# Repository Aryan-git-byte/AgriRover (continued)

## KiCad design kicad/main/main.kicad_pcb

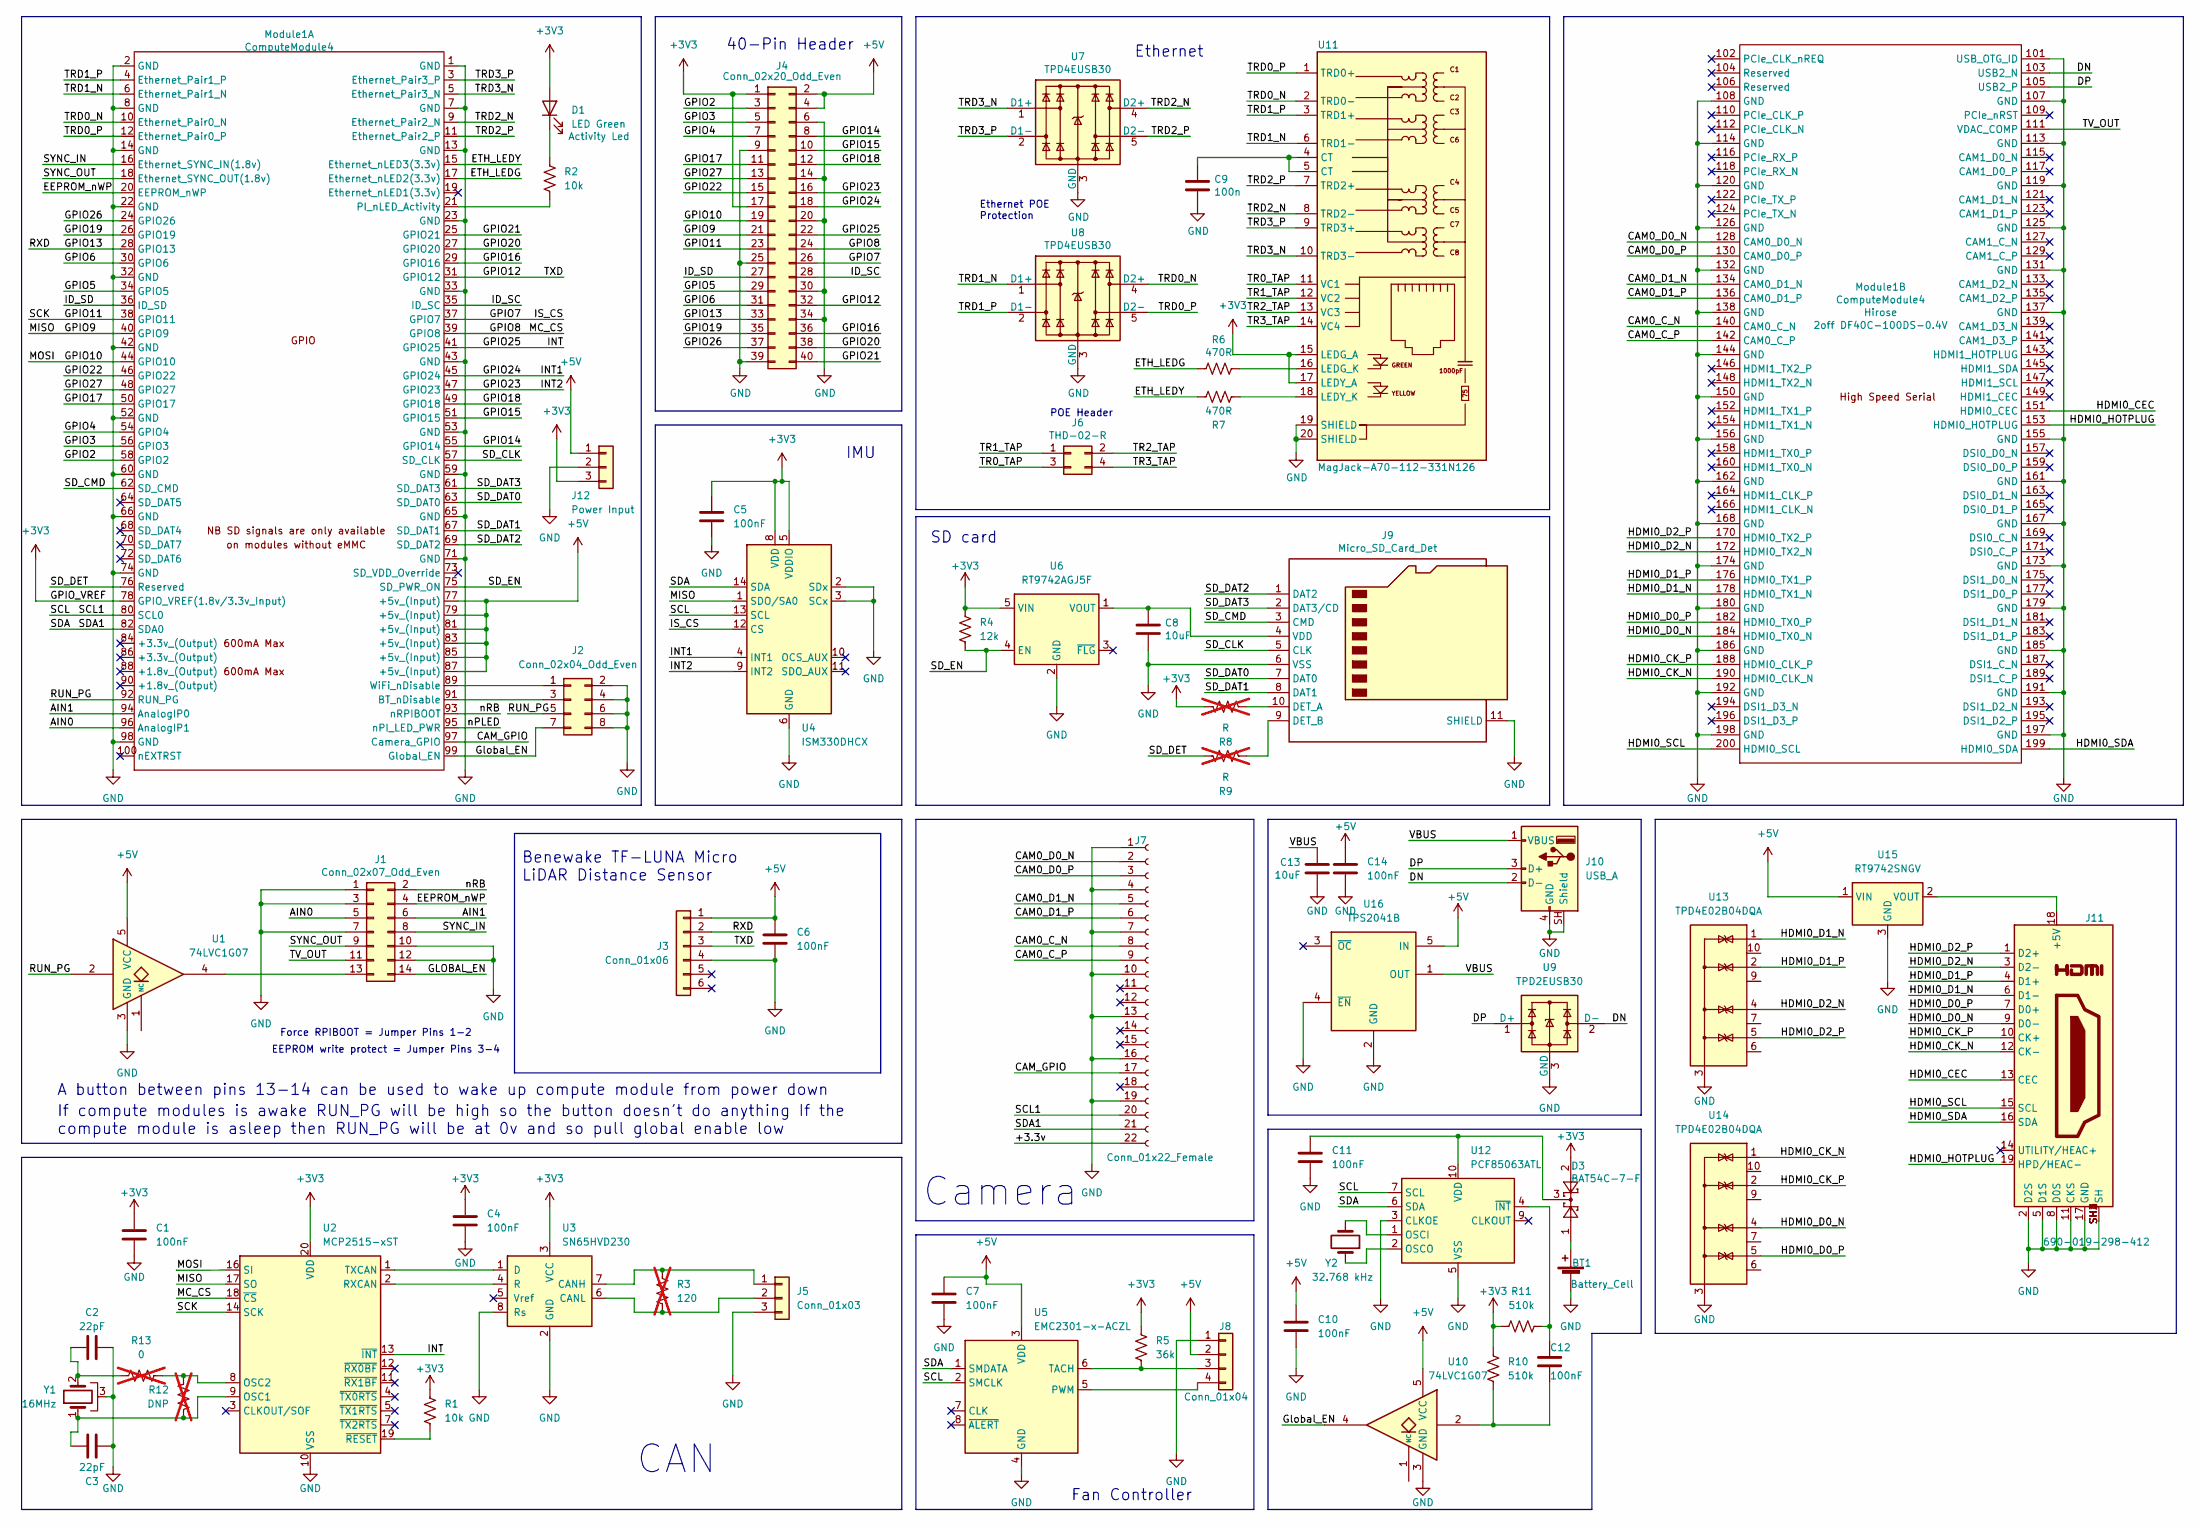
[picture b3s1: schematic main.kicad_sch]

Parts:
BT1: Battery_Cell; BatteryHolder_Keystone_3034_1x20mm; Part Description Battery Retainer Coin, 20.0mm 1 Cell SM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
C1, C4, C5, C6, C7, C10, C11, C12, C14: 100nF; C_0603_1608Metric
C2, C3: 22pF; C_0603_1608Metric
C8, C13: 10uF; C_0805_2012Metric; Part Description 10uF 10% 10V Ceramic Capacitor X7R 0805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
C9: 100n; C_0402_1005Metric; Part Description 0.1uF 10% 16V Ceramic Capacitor X7R 040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
D1: LED Green; LED_0805_2012Metric
D3: BAT54C-7-F; SOT-23; Part Description Diode Array 1 Pair Common Cathode Schot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
J1: Conn_02x07_Odd_Even; PinHeader_2x07_P2.54mm_Vertical; Part Description PinHeader_2x07_P2.54mm_Vertical
J2: Conn_02x04_Odd_Even; PinHeader_2x04_P2.54mm_Vertical
J3: Conn_01x06; Molex_PicoBlade_53047-0610_1x06_P1.25mm_Vertical
J4: Conn_02x20_Odd_Even; PinHeader_2x20_P2.54mm_Vertical; Part Description PinHeader_2x20_P2.54mm_Vertical
J5: Conn_01x03; FanPinHeader_1x03_P2.54mm_Vertical
J6: THD-02-R; PinHeader_2x02_P2.54mm_Vertical; Part Description PinHeader_2x02_P2.54mm_Vertical
J7: Conn_01x22_Female; Hirose_FH12-22S-0.5SH_1x22-1MP_P0.50mm_Horizontal; Part Description 22 Position FFC, FPC Connector Contacts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
J8: Conn_01x04; FanPinHeader_1x04_P2.54mm_Vertical
J9: Micro_SD_Card_Det; SDCARD_MOLEX_503398-1892; Part Description 9 (8 + 1) Position Card Connector micro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
J10: USB_A; USB_A_Connfly_DS1095
J11: 690-019-298-412; EDAC 690-019-298-412; Part Description HDMI Connector, Right Angle, 19 Contact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
J12: Power Input; JST_XH_B3B-XH-A_1x03_P2.50mm_Vertical
Module1: ComputeModule4; Raspberry-Pi-4-Compute-Module; Part Description 100 Position Connector Receptacle, Cent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
R1, R2: 10k; R_0603_1608Metric
R3: 120; R_0603_1608Metric; not fitted
R4: 12k; R_0603_1608Metric
R5: 36k; R_0603_1608Metric
R6, R7: 470R; R_0603_1608Metric; Part Description Resistor 470R M1005 1% 63mW
R8, R9: R; R_0603_1608Metric; not fitted
R10, R11: 510k; R_0603_1608Metric
R12: DNP; R_0603_1608Metric; not fitted
R13: 0; R_0603_1608Metric; not fitted
U1, U10: 74LVC1G07; SOT-23-5
U2: MCP2515-xST; TSSOP-20_4.4x6.5mm_P0.65mm
U3: SN65HVD230; SOIC-8_3.9x4.9mm_P1.27mm
U4: ISM330DHCX; LGA-14_3x2.5mm_P0.5mm_LayoutBorder3x4y
U5: EMC2301-x-ACZL; MSOP-8_3x3mm_P0.65mm
U6: RT9742AGJ5F; TSOT-23-5
U7, U8: TPD4EUSB30; USON-10_2.5x1.0mm_P0.5mm; Part Description Quad TVS diode for high speed signals (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
U9: TPD2EUSB30; Texas_DRT-3
U11: MagJack-A70-112-331N126; TRJG0926HENL; Part Description Gigabit Ethernet Magjack
U12: PCF85063ATL; DFN-10-1EP_2.6x2.6mm_P0.5mm_EP1.3x2.2mm
U13, U14: TPD4E02B04DQA; USON-10_2.5x1.0mm_P0.5mm
U15: RT9742SNGV; SOT-23-3
U16: TPS2041B; SOT-23-5
Y1: 16MHz; Crystal_SMD_3225-4Pin_3.2x2.5mm
Y2: 32.768 kHz; Crystal_SMD_3215-2Pin_3.2x1.5mm

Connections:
+3V3: C1.1, C4.1, C5.1, D1.2 (A), D3.2, J4.1, J4.17, J12.3, Module1.78 (GPIO_VREF(1.8v/3.3v_Input)), R1.1, R4.1, R5.1, R8.1, R10.1, R11.1, U2.20 (VDD), U3.3 (VCC), U4.5 (VDDIO), U4.8 (VDD), U6.5 (VIN), U11.15 (LEDG_A), U11.17 (LEDY_A)
+5V: C6.1, C7.1, C10.1, C14.1, J3.1, J4.2, J4.4, J8.2, J12.1, Module1.77 (+5v_(Input)), Module1.79 (+5v_(Input)), Module1.81 (+5v_(Input)), Module1.83 (+5v_(Input)), Module1.85 (+5v_(Input)), Module1.87 (+5v_(Input)), U1.5 (VCC), U5.3 (VDD), U10.5 (VCC), U15.1 (VIN), U16.5 (IN)
/+3.3v: J7.22
/AIN0: J1.5, Module1.96 (AnalogIP1)
/AIN1: J1.6, Module1.94 (AnalogIP0)
/CAM0_C_N: J7.8, Module1.140 (CAM0_C_N)
/CAM0_C_P: J7.9, Module1.142 (CAM0_C_P)
/CAM0_D0_N: J7.2, Module1.128 (CAM0_D0_N)
/CAM0_D0_P: J7.3, Module1.130 (CAM0_D0_P)
/CAM0_D1_N: J7.5, Module1.134 (CAM0_D1_N)
/CAM0_D1_P: J7.6, Module1.136 (CAM0_D1_P)
/CAM_GPIO: J7.17, Module1.97 (Camera_GPIO)
/DN: J10.2 (D-), Module1.103 (USB2_N), U9.2 (D-)
/DP: J10.3 (D+), Module1.105 (USB2_P), U9.1 (D+)
/EEPROM_nWP: J1.4, Module1.20 (EEPROM_nWP)
/ETH_LEDG: Module1.17 (Ethernet_nLED2(3.3v)), R6.2
/ETH_LEDY: Module1.15 (Ethernet_nLED3(3.3v)), R7.2
/GLOBAL_EN: J1.14
/GPIO2: J4.3, Module1.58 (GPIO2)
/GPIO3: J4.5, Module1.56 (GPIO3)
/GPIO4: J4.7, Module1.54 (GPIO4)
/GPIO5: J4.29, Module1.34 (GPIO5)
/GPIO6: J4.31, Module1.30 (GPIO6)
/GPIO7: J4.26, Module1.37 (GPIO7), U4.12 (CS)
/GPIO8: J4.24, Module1.39 (GPIO8), U2.18 (~CS)
/GPIO9: J4.21, Module1.40 (GPIO9), U2.17 (SO), U4.1 (SDO/SA0)
/GPIO10: J4.19, Module1.44 (GPIO10), U2.16 (SI)
/GPIO11: J4.23, Module1.38 (GPIO11), U2.14 (SCK)
/GPIO12: J3.3, J4.32, Module1.31 (GPIO12)
/GPIO13: J3.2, J4.33, Module1.28 (GPIO13)
/GPIO14: J4.8, Module1.55 (GPIO14)
/GPIO15: J4.10, Module1.51 (GPIO15)
/GPIO16: J4.36, Module1.29 (GPIO16)
/GPIO17: J4.11, Module1.50 (GPIO17)
/GPIO18: J4.12, Module1.49 (GPIO18)
/GPIO19: J4.35, Module1.26 (GPIO19)
/GPIO20: J4.38, Module1.27 (GPIO20)
/GPIO21: J4.40, Module1.25 (GPIO21)
/GPIO22: J4.15, Module1.46 (GPIO22)
/GPIO23: J4.16, Module1.47 (GPIO23), U4.9 (INT2)
/GPIO24: J4.18, Module1.45 (GPIO24), U4.4 (INT1)
/GPIO25: J4.22, Module1.41 (GPIO25), U2.13 (~INT)
/GPIO26: J4.37, Module1.24 (GPIO26)
/GPIO27: J4.13, Module1.48 (GPIO27)
/Global_EN: J2.7, Module1.99 (Global_EN), U10.4
/HDMI0_CEC: J11.13 (CEC), Module1.151 (HDMI0_CEC)
/HDMI0_CK_N: J11.12 (CK-), Module1.190 (HDMI0_CLK_N), U14.1 (IO1)
/HDMI0_CK_P: J11.10 (CK+), Module1.188 (HDMI0_CLK_P), U14.2 (IO2)
/HDMI0_D0_N: J11.9 (D0-), Module1.184 (HDMI0_TX0_N), U14.4 (IO3)
/HDMI0_D0_P: J11.7 (D0+), Module1.182 (HDMI0_TX0_P), U14.5 (IO4)
/HDMI0_D1_N: J11.6 (D1-), Module1.178 (HDMI0_TX1_N), U13.1 (IO1)
/HDMI0_D1_P: J11.4 (D1+), Module1.176 (HDMI0_TX1_P), U13.2 (IO2)
/HDMI0_D2_N: J11.3 (D2-), Module1.172 (HDMI0_TX2_N), U13.4 (IO3)
/HDMI0_D2_P: J11.1 (D2+), Module1.170 (HDMI0_TX2_P), U13.5 (IO4)
/HDMI0_HOTPLUG: J11.19 (HPD/HEAC-), Module1.153 (HDMI0_HOTPLUG)
/HDMI0_SCL: J11.15 (SCL), Module1.200 (HDMI0_SCL)
/HDMI0_SDA: J11.16 (SDA), Module1.199 (HDMI0_SDA)
/ID_SC: J4.28, Module1.35 (ID_SC)
/ID_SD: J4.27, Module1.36 (ID_SD)
/RUN_PG: J2.5, Module1.92 (RUN_PG), U1.2
/SCL: J7.20, Module1.80 (SCL0), U4.13 (SCL), U5.2 (SMCLK), U12.7 (SCL)
/SDA: J7.21, Module1.82 (SDA0), U4.14 (SDA), U5.1 (SMDATA), U12.6 (SDA)
/SD_CLK: J9.5 (CLK), Module1.57 (SD_CLK)
/SD_CMD: J9.3 (CMD), Module1.62 (SD_CMD)
/SD_DAT0: J9.7 (DAT0), Module1.63 (SD_DAT0)
/SD_DAT1: J9.8 (DAT1), Module1.67 (SD_DAT1)
/SD_DAT2: J9.1 (DAT2), Module1.69 (SD_DAT2)
/SD_DAT3: J9.2 (DAT3/CD), Module1.61 (SD_DAT3)
/SD_DET: Module1.76 (Reserved), R9.1
/SD_EN: Module1.75 (SD_PWR_ON), R4.2, U6.4 (EN)
/SYNC_IN: J1.8, Module1.16 (Ethernet_SYNC_IN(1.8v))
/SYNC_OUT: J1.9, Module1.18 (Ethernet_SYNC_OUT(1.8v))
/TR0_TAP: J6.3, U11.11 (VC1)
/TR1_TAP: J6.1, U11.12 (VC2)
/TR2_TAP: J6.2, U11.13 (VC3)
/TR3_TAP: J6.4, U11.14 (VC4)
/TRD0_N: Module1.10 (Ethernet_Pair0_N), U8.4 (D2+), U8.7, U11.2 (TRD0-)
/TRD0_P: Module1.12 (Ethernet_Pair0_P), U8.5 (D2-), U8.6, U11.1 (TRD0+)
/TRD1_N: Module1.6 (Ethernet_Pair1_N), U8.1 (D1+), U8.10, U11.6 (TRD1-)
/TRD1_P: Module1.4 (Ethernet_Pair1_P), U8.2 (D1-), U8.9, U11.3 (TRD1+)
/TRD2_N: Module1.9 (Ethernet_Pair2_N), U7.4 (D2+), U7.7, U11.8 (TRD2-)
/TRD2_P: Module1.11 (Ethernet_Pair2_P), U7.5 (D2-), U7.6, U11.7 (TRD2+)
/TRD3_N: Module1.5 (Ethernet_Pair3_N), U7.1 (D1+), U7.10, U11.10 (TRD3-)
/TRD3_P: Module1.3 (Ethernet_Pair3_P), U7.2 (D1-), U7.9, U11.9 (TRD3+)
/TV_OUT: J1.11, Module1.111 (VDAC_COMP)
/VBUS: C13.1, J10.1 (VBUS), U16.1 (OUT)
/nPLED: Module1.95 (nPI_LED_PWR)
/nRB: J1.2, Module1.93 (nRPIBOOT)
GND: BT1.2 (-), C1.2, C2.2, C3.2, C4.2, C5.2, C6.2, C7.2, C8.2, C9.2, C10.2, C11.2, C13.2, C14.2, J1.1, J1.3, J1.7, J1.10, J1.12, J2.2, J2.4, J2.6, J2.8, J3.4, J4.6, J4.9, J4.14, J4.20, J4.25, J4.30, J4.34, J4.39, J5.3, J7.1, J7.4, J7.7, J7.10, J7.13, J7.16, J7.19, J8.1, J9.6 (VSS), J9.11 (SHIELD), J10.4 (GND), J10.SH (Shield), J11.2 (D2S), J11.5 (D1S), J11.8 (D0S), J11.11 (CKS), J11.17 (GND), J11.SH1 (SH), J11.SH2 (SH), J11.SH3 (SH), J11.SH4 (SH), J12.2, Module1.1 (GND), Module1.2 (GND), Module1.7 (GND), Module1.8 (GND), Module1.13 (GND), Module1.14 (GND), Module1.22 (GND), Module1.23 (GND), Module1.32 (GND), Module1.33 (GND), Module1.42 (GND), Module1.43 (GND), Module1.52 (GND), Module1.53 (GND), Module1.59 (GND), Module1.60 (GND), Module1.65 (GND), Module1.66 (GND), Module1.71 (GND), Module1.74 (GND), Module1.98 (GND), Module1.101 (USB_OTG_ID), Module1.107 (GND), Module1.108 (GND), Module1.113 (GND), Module1.114 (GND), Module1.119 (GND), Module1.120 (GND), Module1.125 (GND), Module1.126 (GND), Module1.131 (GND), Module1.132 (GND), Module1.137 (GND), Module1.138 (GND), Module1.144 (GND), Module1.150 (GND), Module1.155 (GND), Module1.156 (GND), Module1.161 (GND), Module1.162 (GND), Module1.167 (GND), Module1.168 (GND), Module1.173 (GND), Module1.174 (GND), Module1.179 (GND), Module1.180 (GND), Module1.185 (GND), Module1.186 (GND), Module1.191 (GND), Module1.192 (GND), Module1.197 (GND), Module1.198 (GND), U1.3 (GND), U2.10 (VSS), U3.2 (GND), U3.8 (Rs), U4.2 (SDx), U4.3 (SCx), U4.6 (GND), U4.7 (GND), U5.4 (GND), U6.2 (GND), U7.3 (GND), U7.8 (GND), U8.3 (GND), U8.8 (GND), U9.3 (GND), U10.3 (GND), U11.19 (SHIELD), U11.20 (SHIELD), U12.3 (CLKOE), U12.5 (VSS), U12.11 (MP), U13.3 (G), U13.8 (G), U14.3 (G), U14.8 (G), U15.3 (GND), U16.2 (GND), U16.4 (~EN), Y1.3, Y1.4 (3)
unnamed: BT1.1 (+), D3.1
unnamed: C2.1, R13.2, Y1.2
unnamed: C9.1, U11.4 (CT), U11.5 (CT)
unnamed: C12.2, R10.2, U10.2
unnamed: D1.1 (K), R2.1
unnamed: J1.13, U1.4
unnamed: J2.1, Module1.89 (WiFi_nDisable)
unnamed: J2.3, Module1.91 (BT_nDisable)
unnamed: J5.1, R3.1, U3.7 (CANH)
unnamed: J5.2, R3.2, U3.6 (CANL)
unnamed: J8.3, R5.2, U5.6 (TACH)
unnamed: J8.4, U5.5 (PWM)
unnamed: J9.10 (DET_A), R8.2
unnamed: J9.9 (DET_B), R9.2
unnamed: C8.1, J9.4 (VDD), U6.1 (VOUT)
unnamed: J11.18 (+5V), U15.2 (VOUT)
unnamed: Module1.21 (PI_nLED_Activity), R2.2
unnamed: C3.1, R12.2, U2.9 (OSC1), Y1.1
unnamed: R12.1, R13.1, U2.8 (OSC2)
unnamed: U2.2 (RXCAN), U3.4 (R)
unnamed: U2.1 (TXCAN), U3.1 (D)
unnamed: R1.2, U2.19 (~RESET)
unnamed: R6.1, U11.16 (LEDG_K)
unnamed: R7.1, U11.18 (LEDY_K)
unnamed: U12.1 (OSCI), Y2.2
unnamed: U12.2 (OSCO), Y2.1
unnamed: C11.1, D3.3, U12.10 (VDD)
unnamed: C12.1, R11.2, U12.4 (~INT)

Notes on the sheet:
POE Header
IMU
A button between pins 13-14 can be used to wake up compute module from power down
If compute modules is awake RUN_PG will be high so the button doesn't do anything If the compute module is asleep then RUN_PG will be at 0v and so pull global enable low
Fan Controller
CAN
40-Pin Header
Ethernet
Benewake TF-LUNA Micro LiDAR Distance Sensor
Force RPIBOOT = Jumper Pins 1-2
SD card
Camera
EEPROM write protect = Jumper Pins 3-4
Ethernet POE Protection

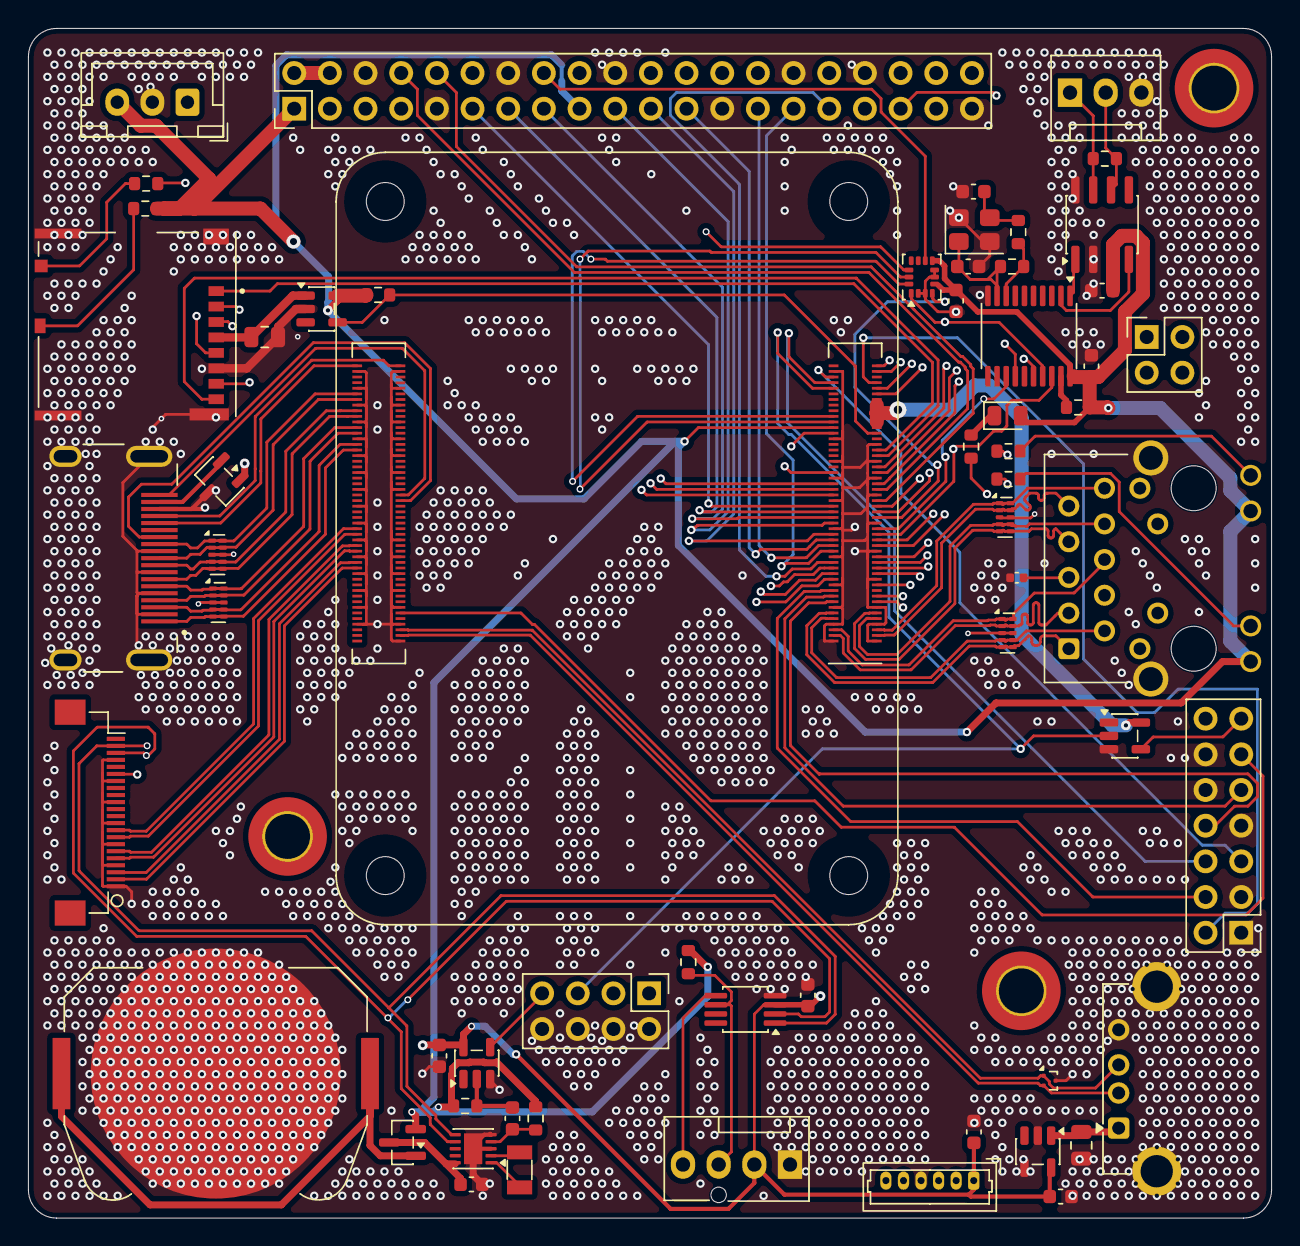
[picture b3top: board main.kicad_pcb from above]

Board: 6 copper layers, 88.5 x 84.7 mm, 61 parts (0 on the bottom side), 114 nets.

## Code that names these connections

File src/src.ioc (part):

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Mcu.Name=STM32G431R(6-8-B)Tx
Mcu.Package=LQFP64
Mcu.UserName=STM32G431R6Tx
PA0.Signal=S_TIM2_CH1
PA1.Signal=S_TIM2_CH2
PA10.Signal=S_TIM1_CH3
PA11.Signal=S_TIM1_CH4
PA13.Mode=Serial_Wire
PA13.Signal=SYS_JTMS-SWDIO
PA14.Mode=Serial_Wire
PA14.Signal=SYS_JTCK-SWCLK
PA6.Signal=S_TIM3_CH1
PA7.Signal=S_TIM3_CH2
PA8.Signal=S_TIM1_CH1
PA9.Signal=S_TIM1_CH2
PB10.Signal=GPIO_Output
PB11.Signal=GPIO_Output
PB12.Signal=GPIO_Output
PB13.Signal=GPIO_Output
PB14.Signal=S_TIM15_CH1
PB2.Signal=GPIO_Output
PB6.Signal=S_TIM4_CH1
PB7.Signal=S_TIM4_CH2
PC0.Mode=IN6-Differential
PC0.Signal=ADC1_IN6
PC1.Mode=IN6-Differential
PC1.Signal=ADC1_IN7
PC10.Signal=GPIO_Input
PC11.Signal=GPIO_Input
PC12.Signal=GPIO_Input
PC2.Mode=IN8-Differential
PC2.Signal=ADC1_IN8
PC3.Mode=IN8-Differential
PC3.Signal=ADC1_IN9
PC4.Signal=GPIO_Input
PC6.Signal=S_TIM8_CH1
PC7.Signal=S_TIM8_CH2
PD2.Signal=GPIO_Input
RCC.HSE_VALUE=8000000
RCC.SYSCLKFreq_VALUE=170000000
RCC.SYSCLKSource=RCC_SYSCLKSOURCE_PLLCLK
board=custom
